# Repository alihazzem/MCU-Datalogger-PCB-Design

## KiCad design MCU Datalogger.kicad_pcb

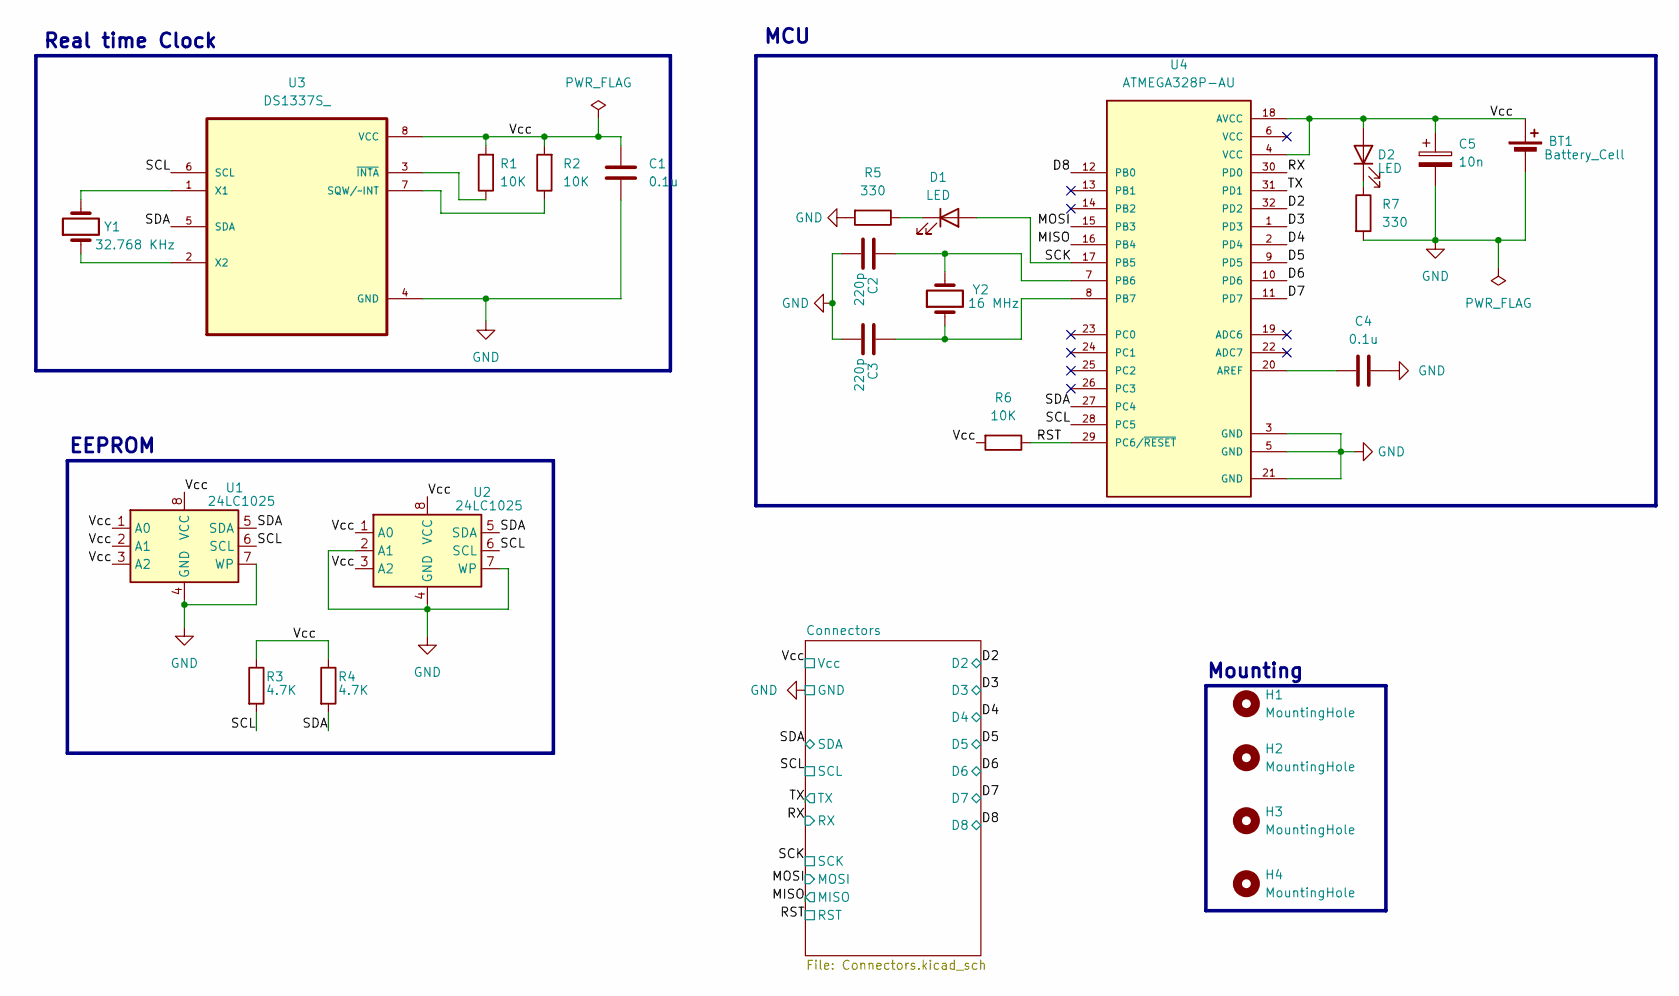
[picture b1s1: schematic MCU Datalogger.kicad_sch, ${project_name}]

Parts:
BT1: Battery_Cell; PinHeader_1x02_P2.54mm_Vertical
C1, C4: 0.1u; C_0805_2012Metric
C2, C3: 220p; C_0805_2012Metric
C5: 10n; C_0805_2012Metric
D1, D2: LED; LED_0805_2012Metric
H1, H2, H3, H4: MountingHole; MountingHole_2.1mm
R1, R2, R6: 10K; R_0805_2012Metric
R3, R4: 4.7K; R_0805_2012Metric
R5, R7: 330; R_0805_2012Metric
U1, U2: 24LC1025; SOIC-8_5.3x5.3mm_P1.27mm
U3: DS1337S_; SOIC127P600X175-8N
U4: ATMEGA328P-AU; QFP80P900X900X120-32N; PARTREV 8271A
Y1: 32.768 KHz; Crystal_SMD_5032-2Pin_5.0x3.2mm_HandSoldering
Y2: 16 MHz; Crystal_SMD_5032-2Pin_5.0x3.2mm_HandSoldering

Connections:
/D2: U4.32 (PD2); also elsewhere on the board
/D3: U4.1 (PD3); also elsewhere on the board
/D4: U4.2 (PD4); also elsewhere on the board
/D5: U4.9 (PD5); also elsewhere on the board
/D6: U4.10 (PD6); also elsewhere on the board
/D7: U4.11 (PD7); also elsewhere on the board
/D8: U4.12 (PB0); also elsewhere on the board
/MISO: U4.16 (PB4); also elsewhere on the board
/MOSI: U4.15 (PB3); also elsewhere on the board
/RST: R6.1, U4.29 (PC6/~RESET); also elsewhere on the board
/RX: U4.30 (PD0); also elsewhere on the board
/SCK: D1.2 (A), U4.17 (PB5); also elsewhere on the board
/SCL: R3.2, U1.6 (SCL), U2.6 (SCL), U3.6 (SCL), U4.28 (PC5); also elsewhere on the board
/SDA: R4.2, U1.5 (SDA), U2.5 (SDA), U3.5 (SDA), U4.27 (PC4); also elsewhere on the board
/TX: U4.31 (PD1); also elsewhere on the board
/Vcc: BT1.1 (+), C1.1, C5.1, D2.2 (A), R1.2, R2.2, R3.1, R4.1, R6.2, U1.1 (A0), U1.2 (A1), U1.3 (A2), U1.8 (VCC), U2.1 (A0), U2.3 (A2), U2.8 (VCC), U3.8 (VCC), U4.4 (VCC), U4.18 (AVCC); also elsewhere on the board
GND: BT1.2 (-), C1.2, C2.2, C3.2, C4.2, C5.2, R5.2, R7.2, U1.4 (GND), U1.7 (WP), U2.2 (A1), U2.4 (GND), U2.7 (WP), U3.4 (GND), U4.3 (GND), U4.5 (GND), U4.21 (GND); also elsewhere on the board
unnamed: D1.1 (K), R5.1
unnamed: D2.1 (K), R7.1
unnamed: R2.1, U3.7 (SQW/~INT)
unnamed: U3.1 (X1), Y1.2
unnamed: U3.2 (X2), Y1.1
unnamed: R1.1, U3.3 (~INTA)
unnamed: C4.1, U4.20 (AREF)
unnamed: C2.1, U4.7 (PB6), Y2.2
unnamed: C3.1, U4.8 (PB7), Y2.1

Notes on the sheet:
Mounting
MCU
Real time Clock
EEPROM

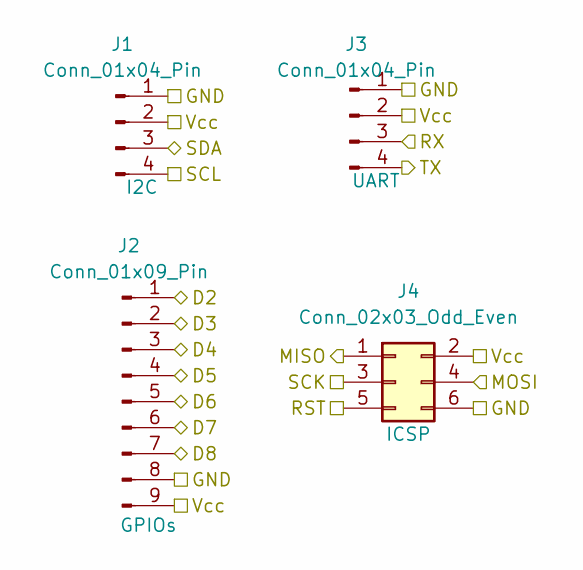
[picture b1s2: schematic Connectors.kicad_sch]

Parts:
J1, J3: Conn_01x04_Pin; PinHeader_1x04_P2.54mm_Vertical
J2: Conn_01x09_Pin; PinHeader_1x09_P2.54mm_Vertical
J4: Conn_02x03_Odd_Even; PinHeader_2x03_P2.54mm_Vertical

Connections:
/D2: J2.1; also elsewhere on the board
/D3: J2.2; also elsewhere on the board
/D4: J2.3; also elsewhere on the board
/D5: J2.4; also elsewhere on the board
/D6: J2.5; also elsewhere on the board
/D7: J2.6; also elsewhere on the board
/D8: J2.7; also elsewhere on the board
/MISO: J4.1; also elsewhere on the board
/MOSI: J4.4; also elsewhere on the board
/RST: J4.5; also elsewhere on the board
/RX: J3.3; also elsewhere on the board
/SCK: J4.3; also elsewhere on the board
/SCL: J1.4; also elsewhere on the board
/SDA: J1.3; also elsewhere on the board
/TX: J3.4; also elsewhere on the board
/Vcc: J1.2, J2.9, J3.2, J4.2; also elsewhere on the board
GND: J1.1, J2.8, J3.1, J4.6; also elsewhere on the board

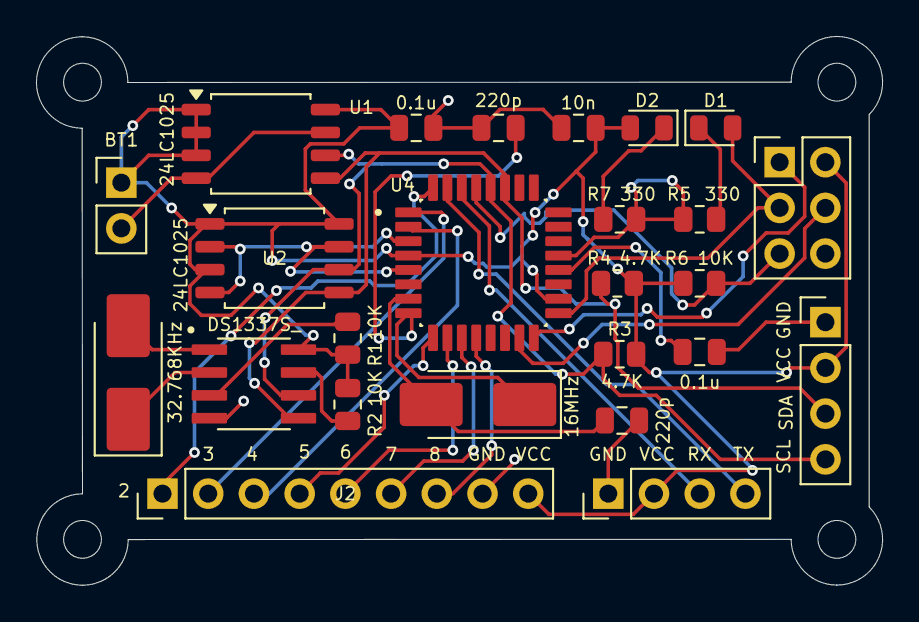
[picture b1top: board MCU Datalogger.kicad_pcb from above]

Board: 2 copper layers, 47.0 x 30.5 mm, 29 parts (0 on the bottom side), 26 nets.
